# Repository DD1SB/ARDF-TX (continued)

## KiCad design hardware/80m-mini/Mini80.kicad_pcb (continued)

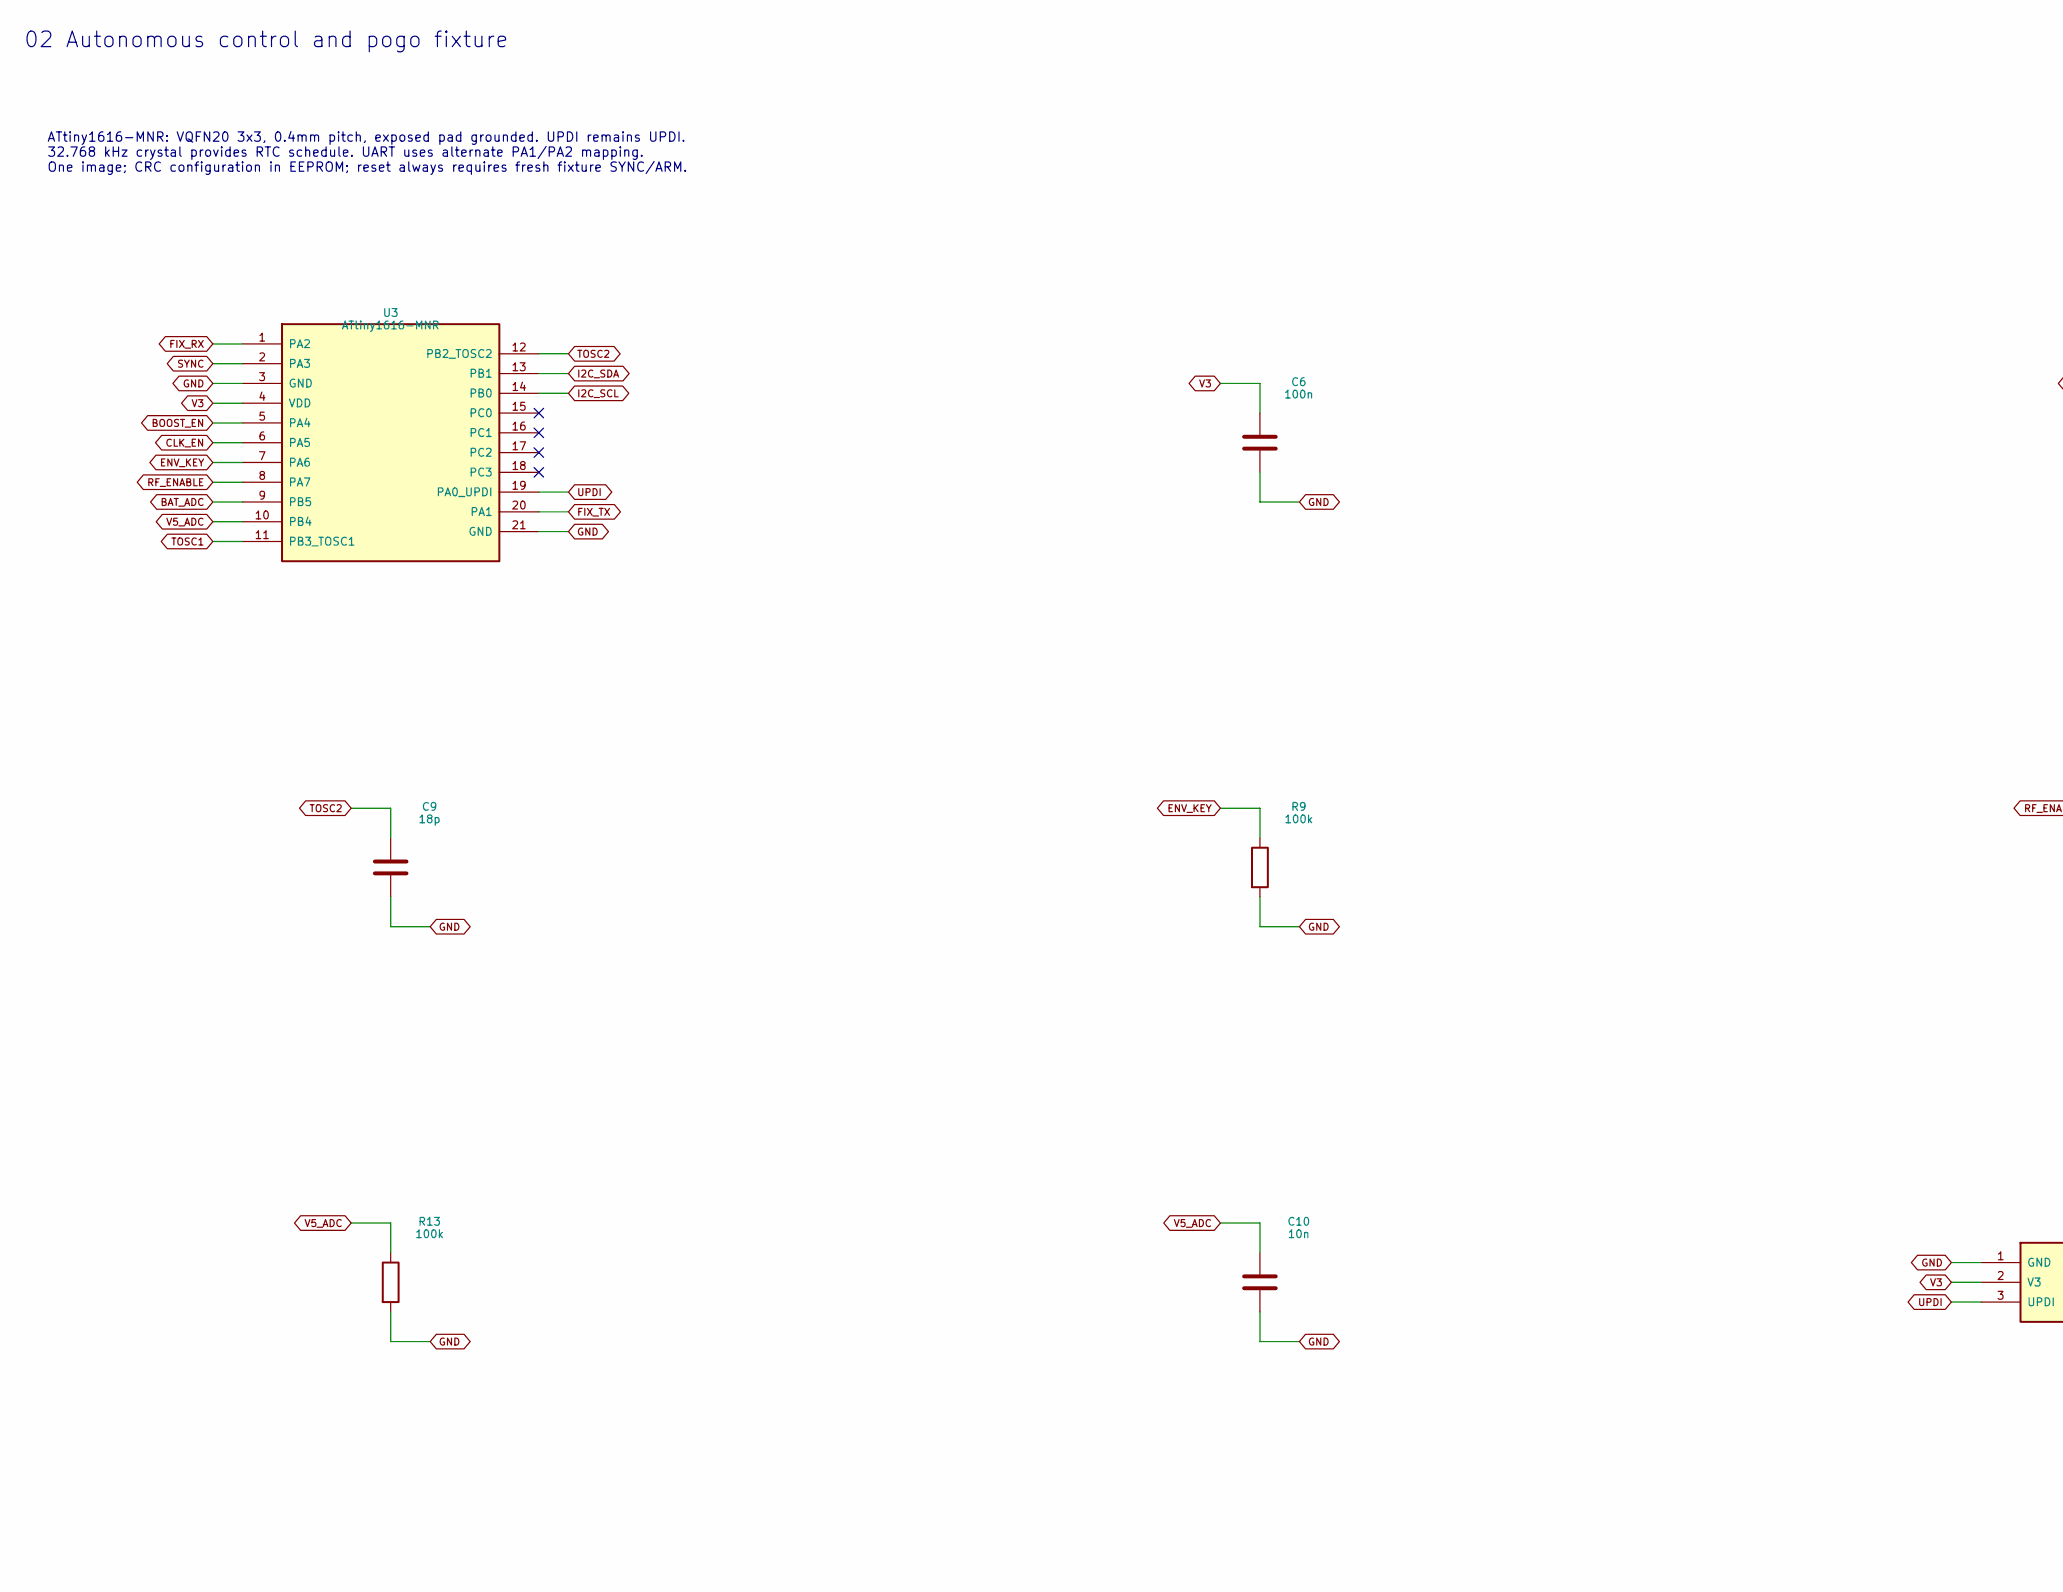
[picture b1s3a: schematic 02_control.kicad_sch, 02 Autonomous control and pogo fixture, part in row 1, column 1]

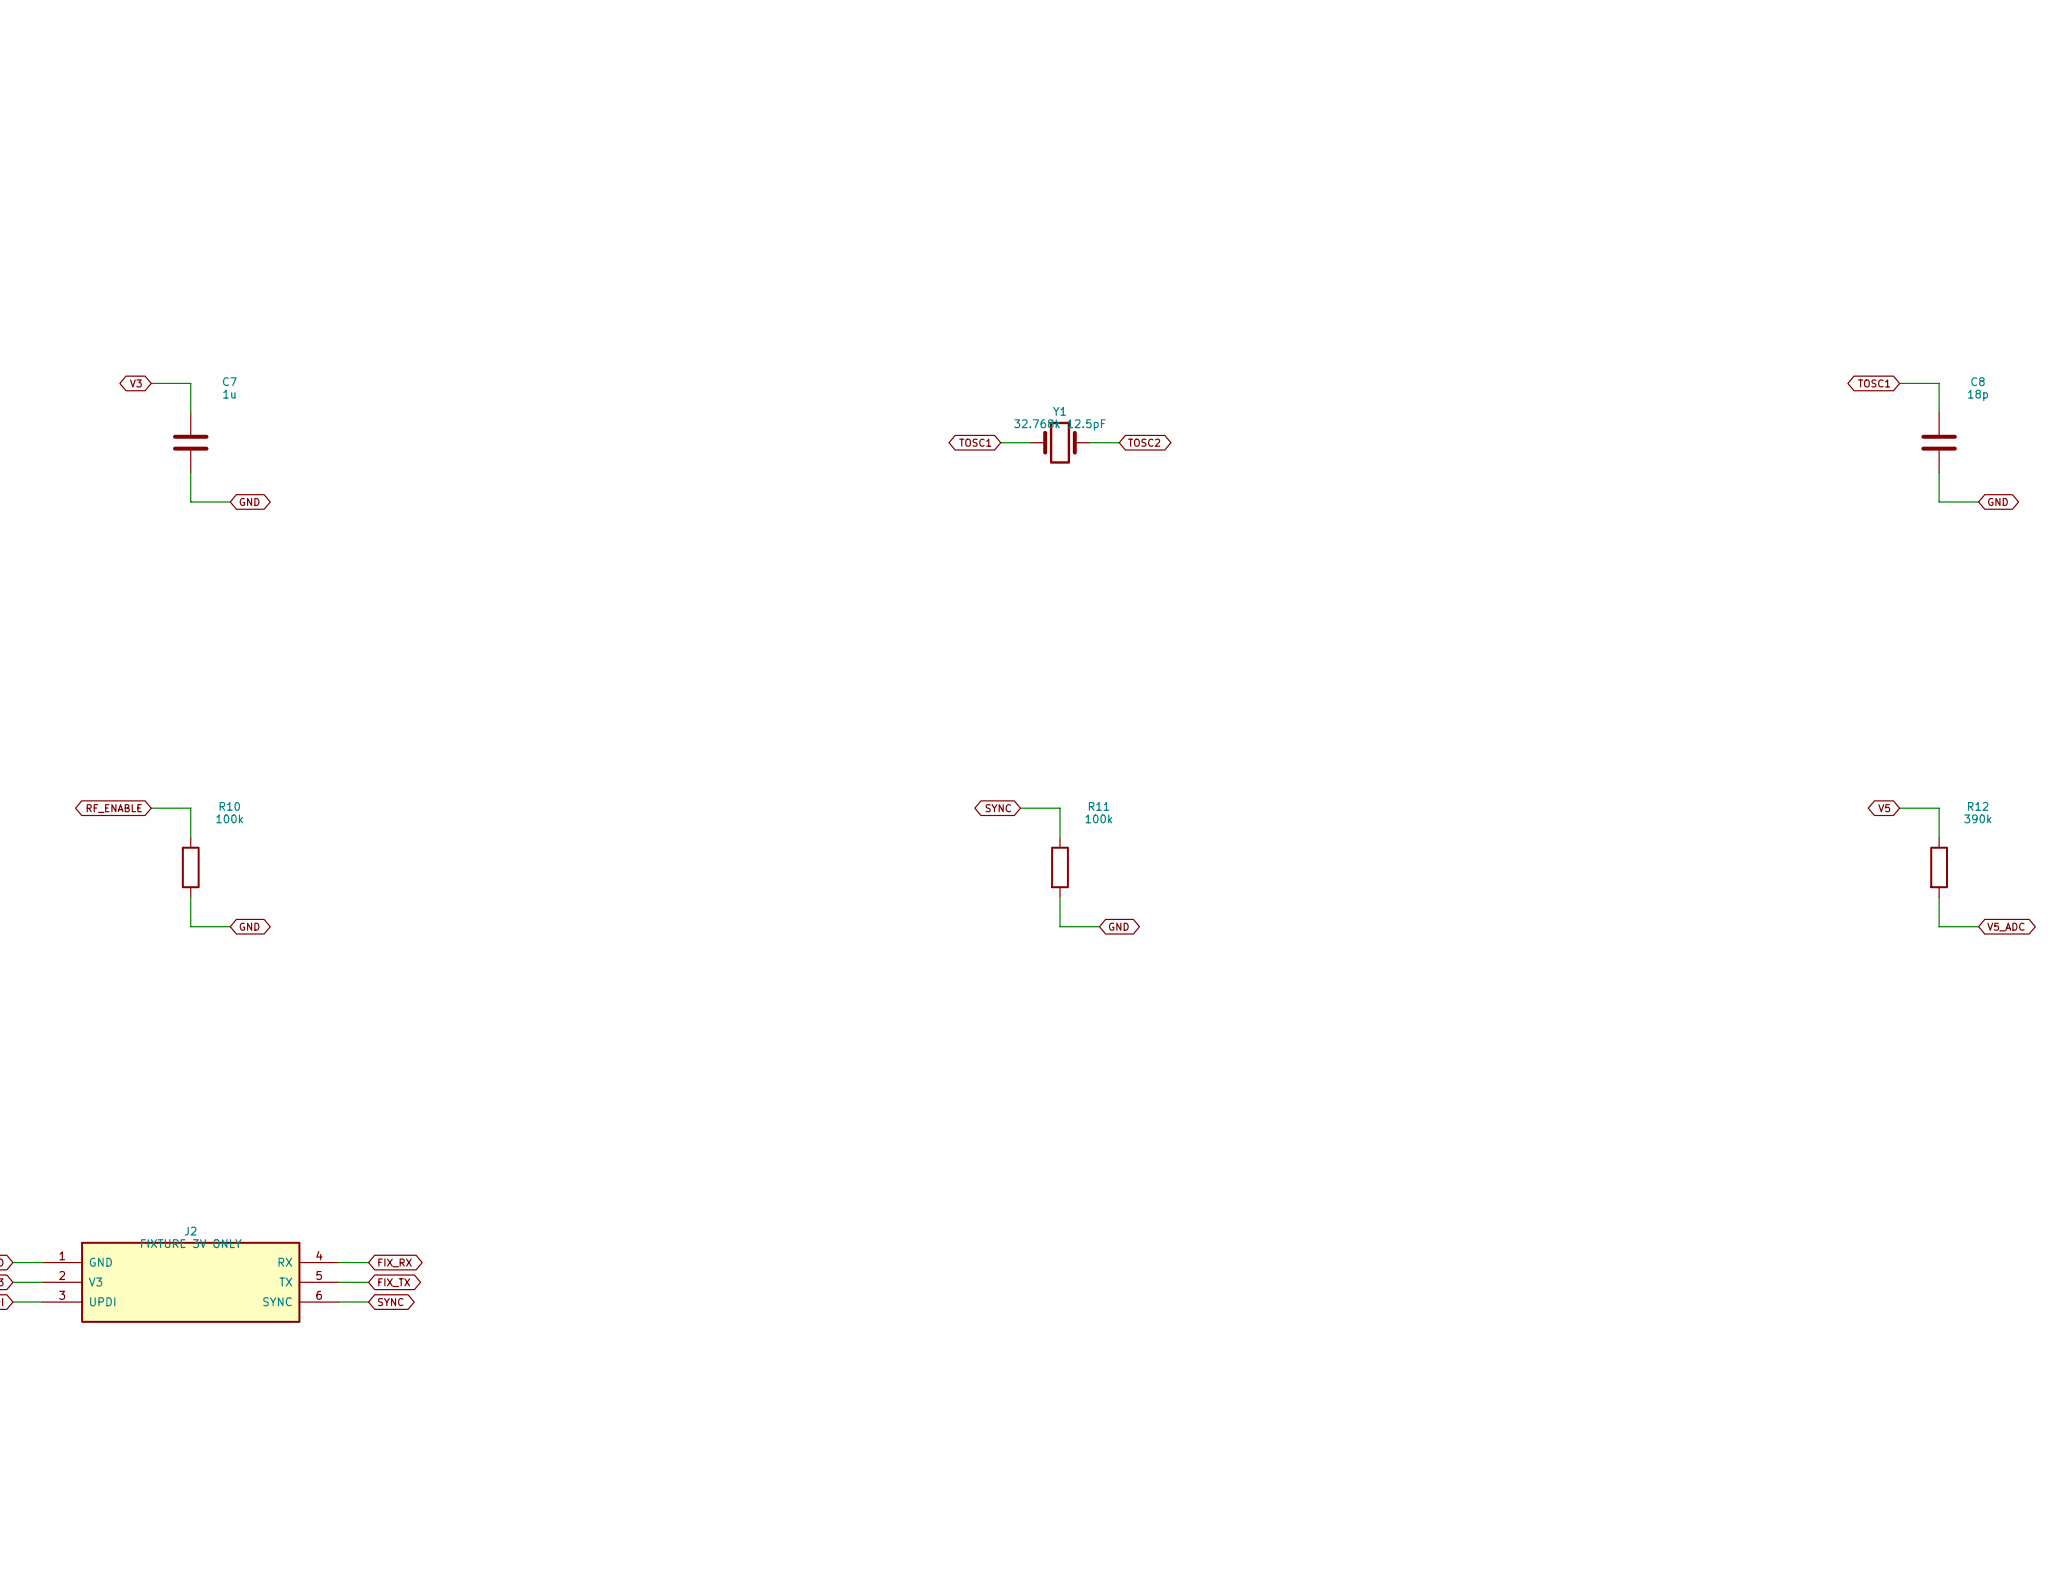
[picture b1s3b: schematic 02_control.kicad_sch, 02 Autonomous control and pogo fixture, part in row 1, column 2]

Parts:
C6: 100n; C_0402_1005Metric; MPN CL05B104KO5NNNC
C7: 1u; C_0402_1005Metric; MPN GRM155R61A105KE15D
C8, C9: 18p; C_0402_1005Metric; MPN GRM1555C1H180JA01D
C10: 10n; C_0402_1005Metric; MPN GRM155R71H103KA88D
J2: FIXTURE 3V ONLY; Pogo6; MPN PCB feature
R9, R10, R11, R13: 100k; R_0402_1005Metric; MPN RC0402FR-07100KL
R12: 390k; R_0402_1005Metric; MPN RC0402FR-07390KL
U3: ATtiny1616-MNR; ATtiny1616_VQFN20_JLC; MPN ATTINY1616-MNR
Y1: 32.768k 12.5pF; Crystal_SMD_3215-2Pin_3.2x1.5mm; MPN ABS07-32.768KHZ-T

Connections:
BAT_ADC: U3.9 (PB5); also elsewhere on the board
BOOST_EN: U3.5 (PA4); also elsewhere on the board
CLK_EN: U3.6 (PA5); also elsewhere on the board
ENV_KEY: R9.1, U3.7 (PA6); also elsewhere on the board
FIX_RX: J2.4 (RX), U3.1 (PA2)
FIX_TX: J2.5 (TX), U3.20 (PA1)
GND: C6.2, C7.2, C8.2, C9.2, C10.2, J2.1 (GND), R9.2, R10.2, R11.2, R13.2, U3.3 (GND), U3.21 (GND); also elsewhere on the board
I2C_SCL: U3.14 (PB0); also elsewhere on the board
I2C_SDA: U3.13 (PB1); also elsewhere on the board
RF_ENABLE: R10.1, U3.8 (PA7); also elsewhere on the board
SYNC: J2.6 (SYNC), R11.1, U3.2 (PA3)
TOSC1: C8.1, U3.11 (PB3_TOSC1), Y1.1
TOSC2: C9.1, U3.12 (PB2_TOSC2), Y1.2
UPDI: J2.3 (UPDI), U3.19 (PA0_UPDI)
V3: C6.1, C7.1, J2.2 (V3), U3.4 (VDD); also elsewhere on the board
V5: R12.1; also elsewhere on the board
V5_ADC: C10.1, R12.2, R13.1, U3.10 (PB4)

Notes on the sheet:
02 Autonomous control and pogo fixture
ATtiny1616-MNR: VQFN20 3x3, 0.4mm pitch, exposed pad grounded. UPDI remains UPDI. 32.768 kHz crystal provides RTC schedule. UART uses alternate PA1/PA2 mapping. One image; CRC configuration in EEPROM; reset always requires fresh fixture SYNC/ARM.
M80-E1: REVIEW / ALL hardware measurements NOT RUN / unbuilt engineering candidate.

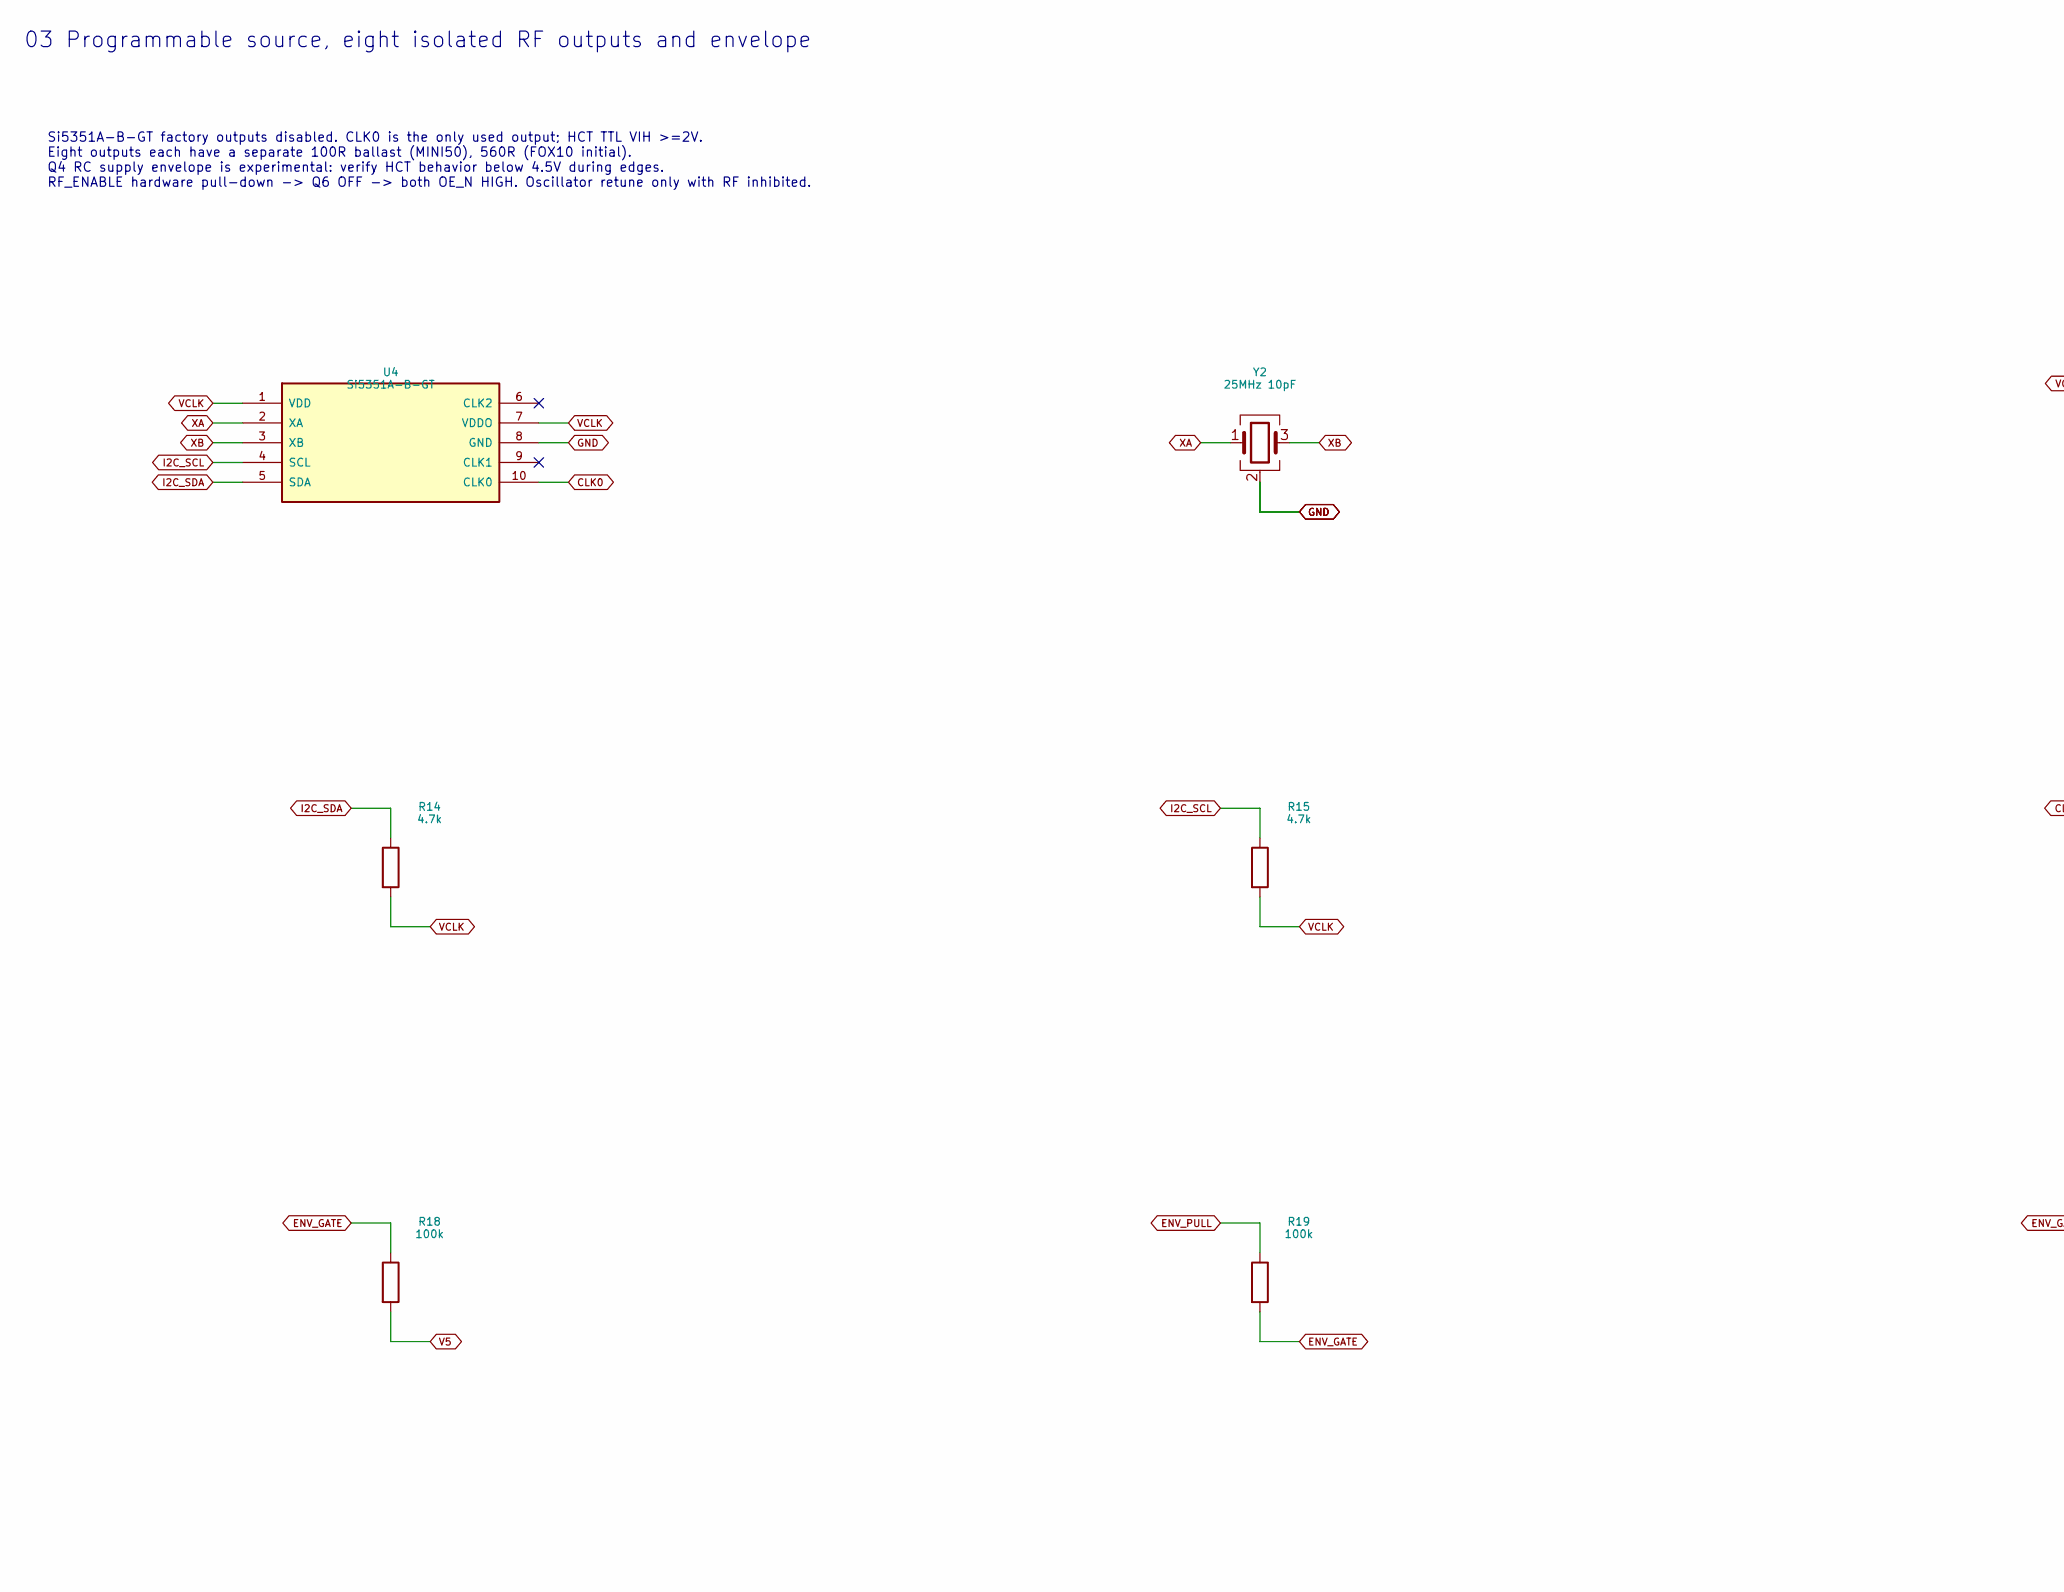
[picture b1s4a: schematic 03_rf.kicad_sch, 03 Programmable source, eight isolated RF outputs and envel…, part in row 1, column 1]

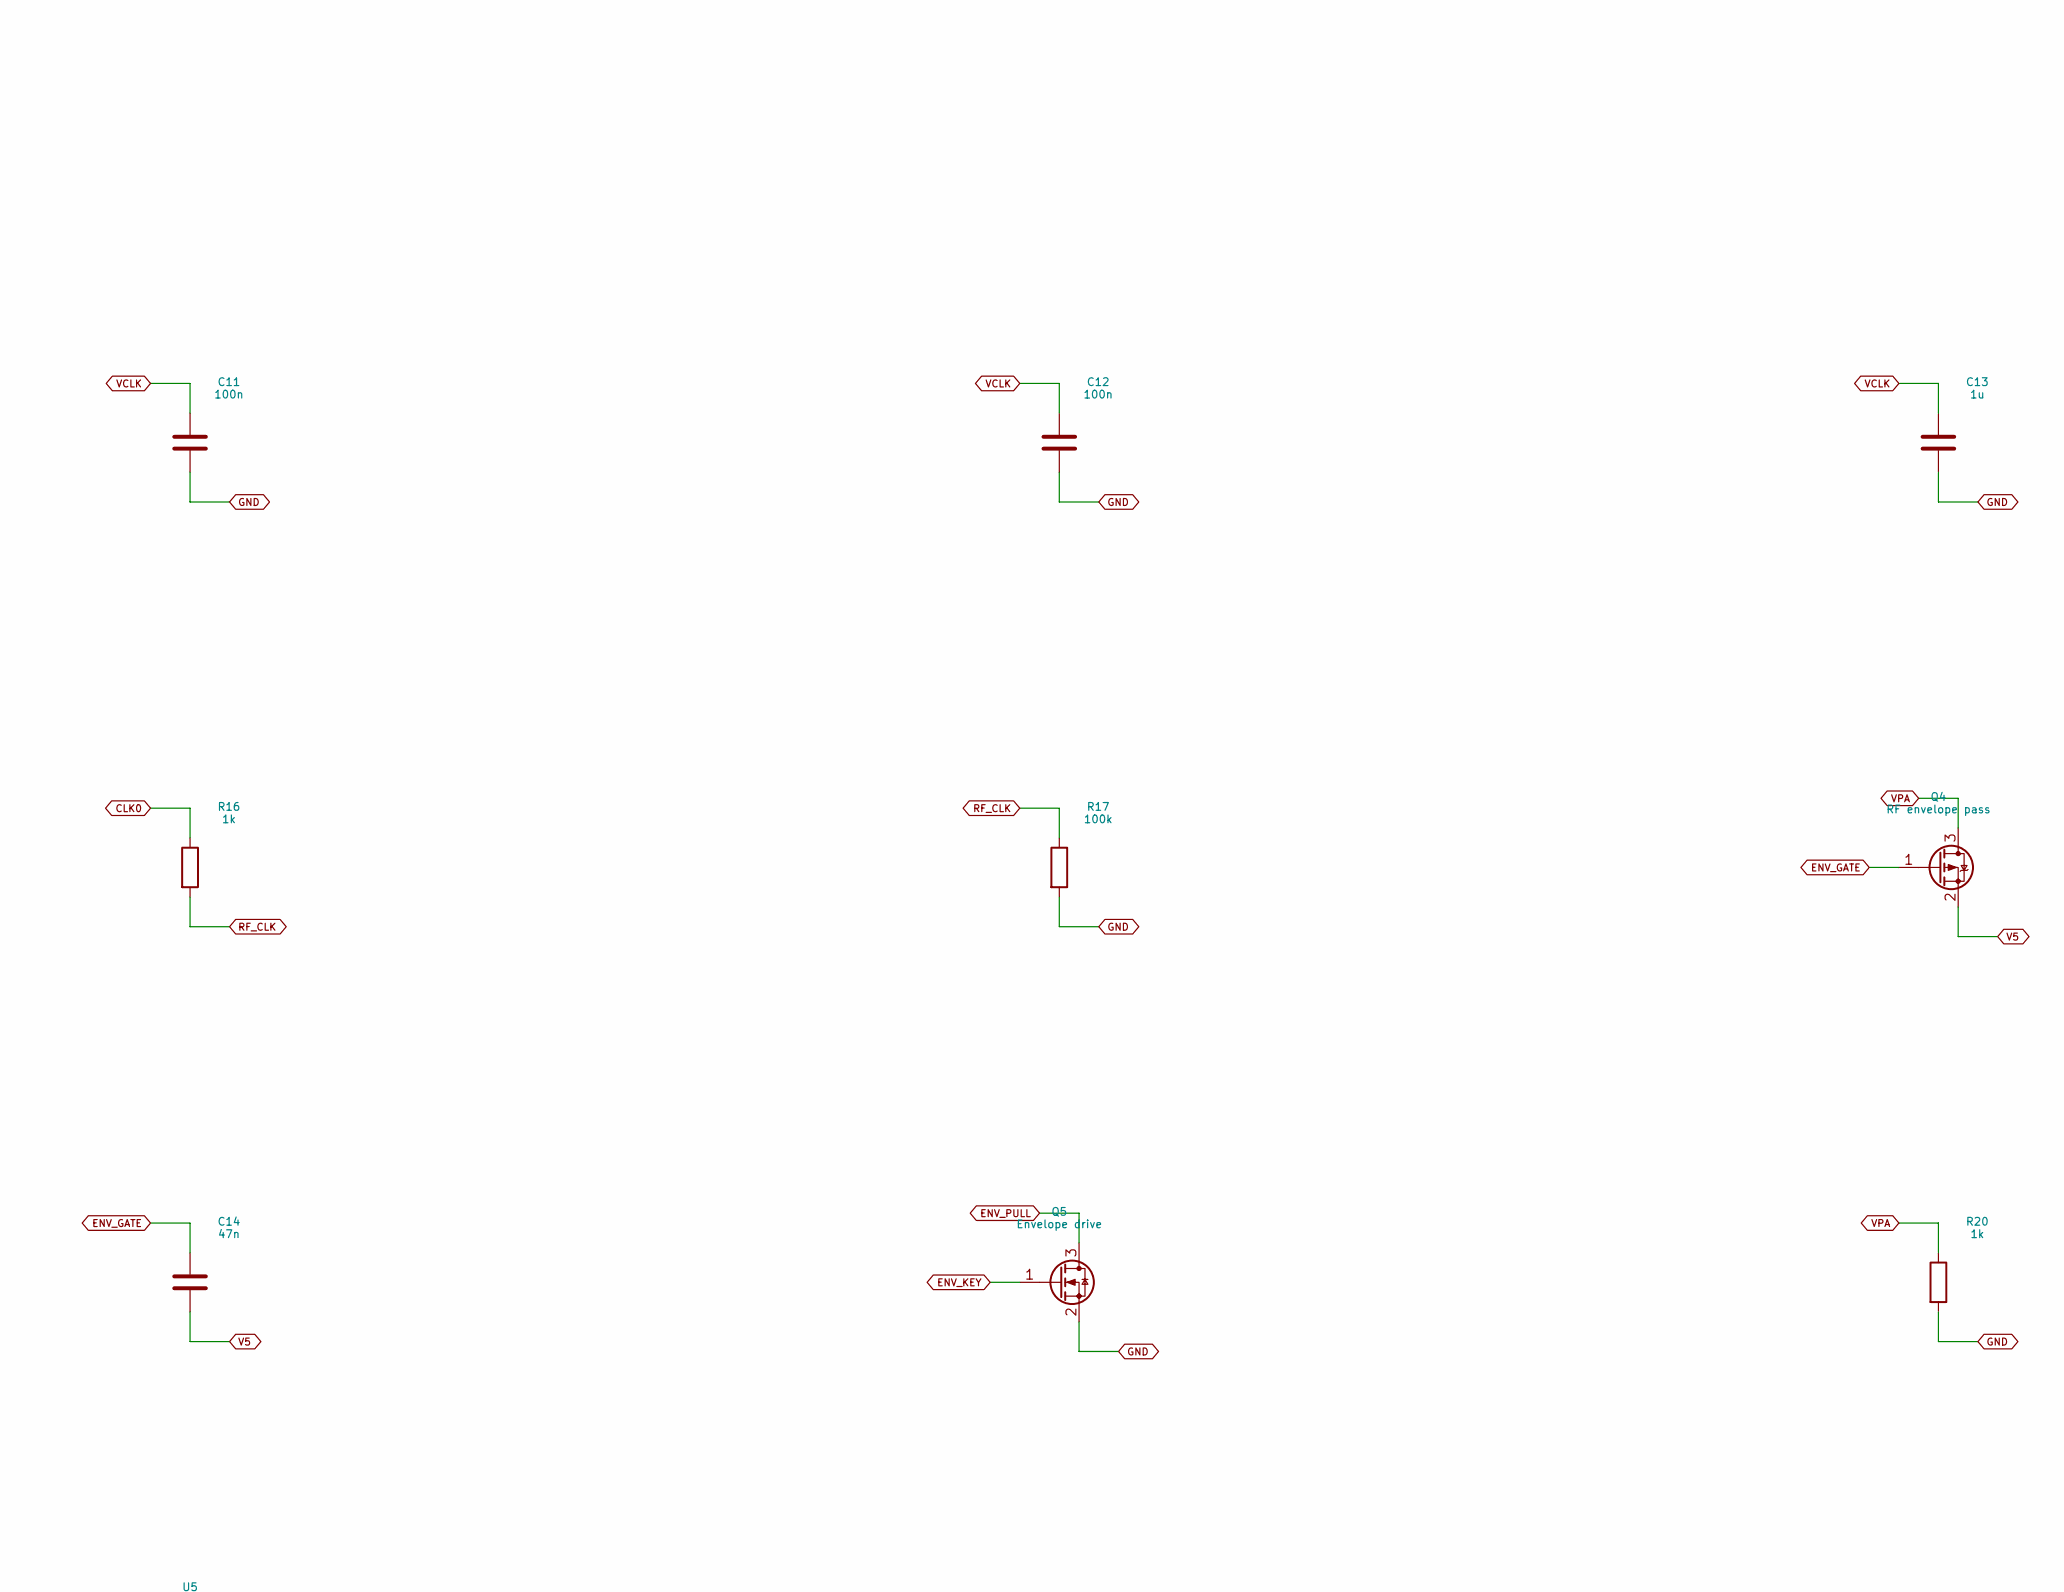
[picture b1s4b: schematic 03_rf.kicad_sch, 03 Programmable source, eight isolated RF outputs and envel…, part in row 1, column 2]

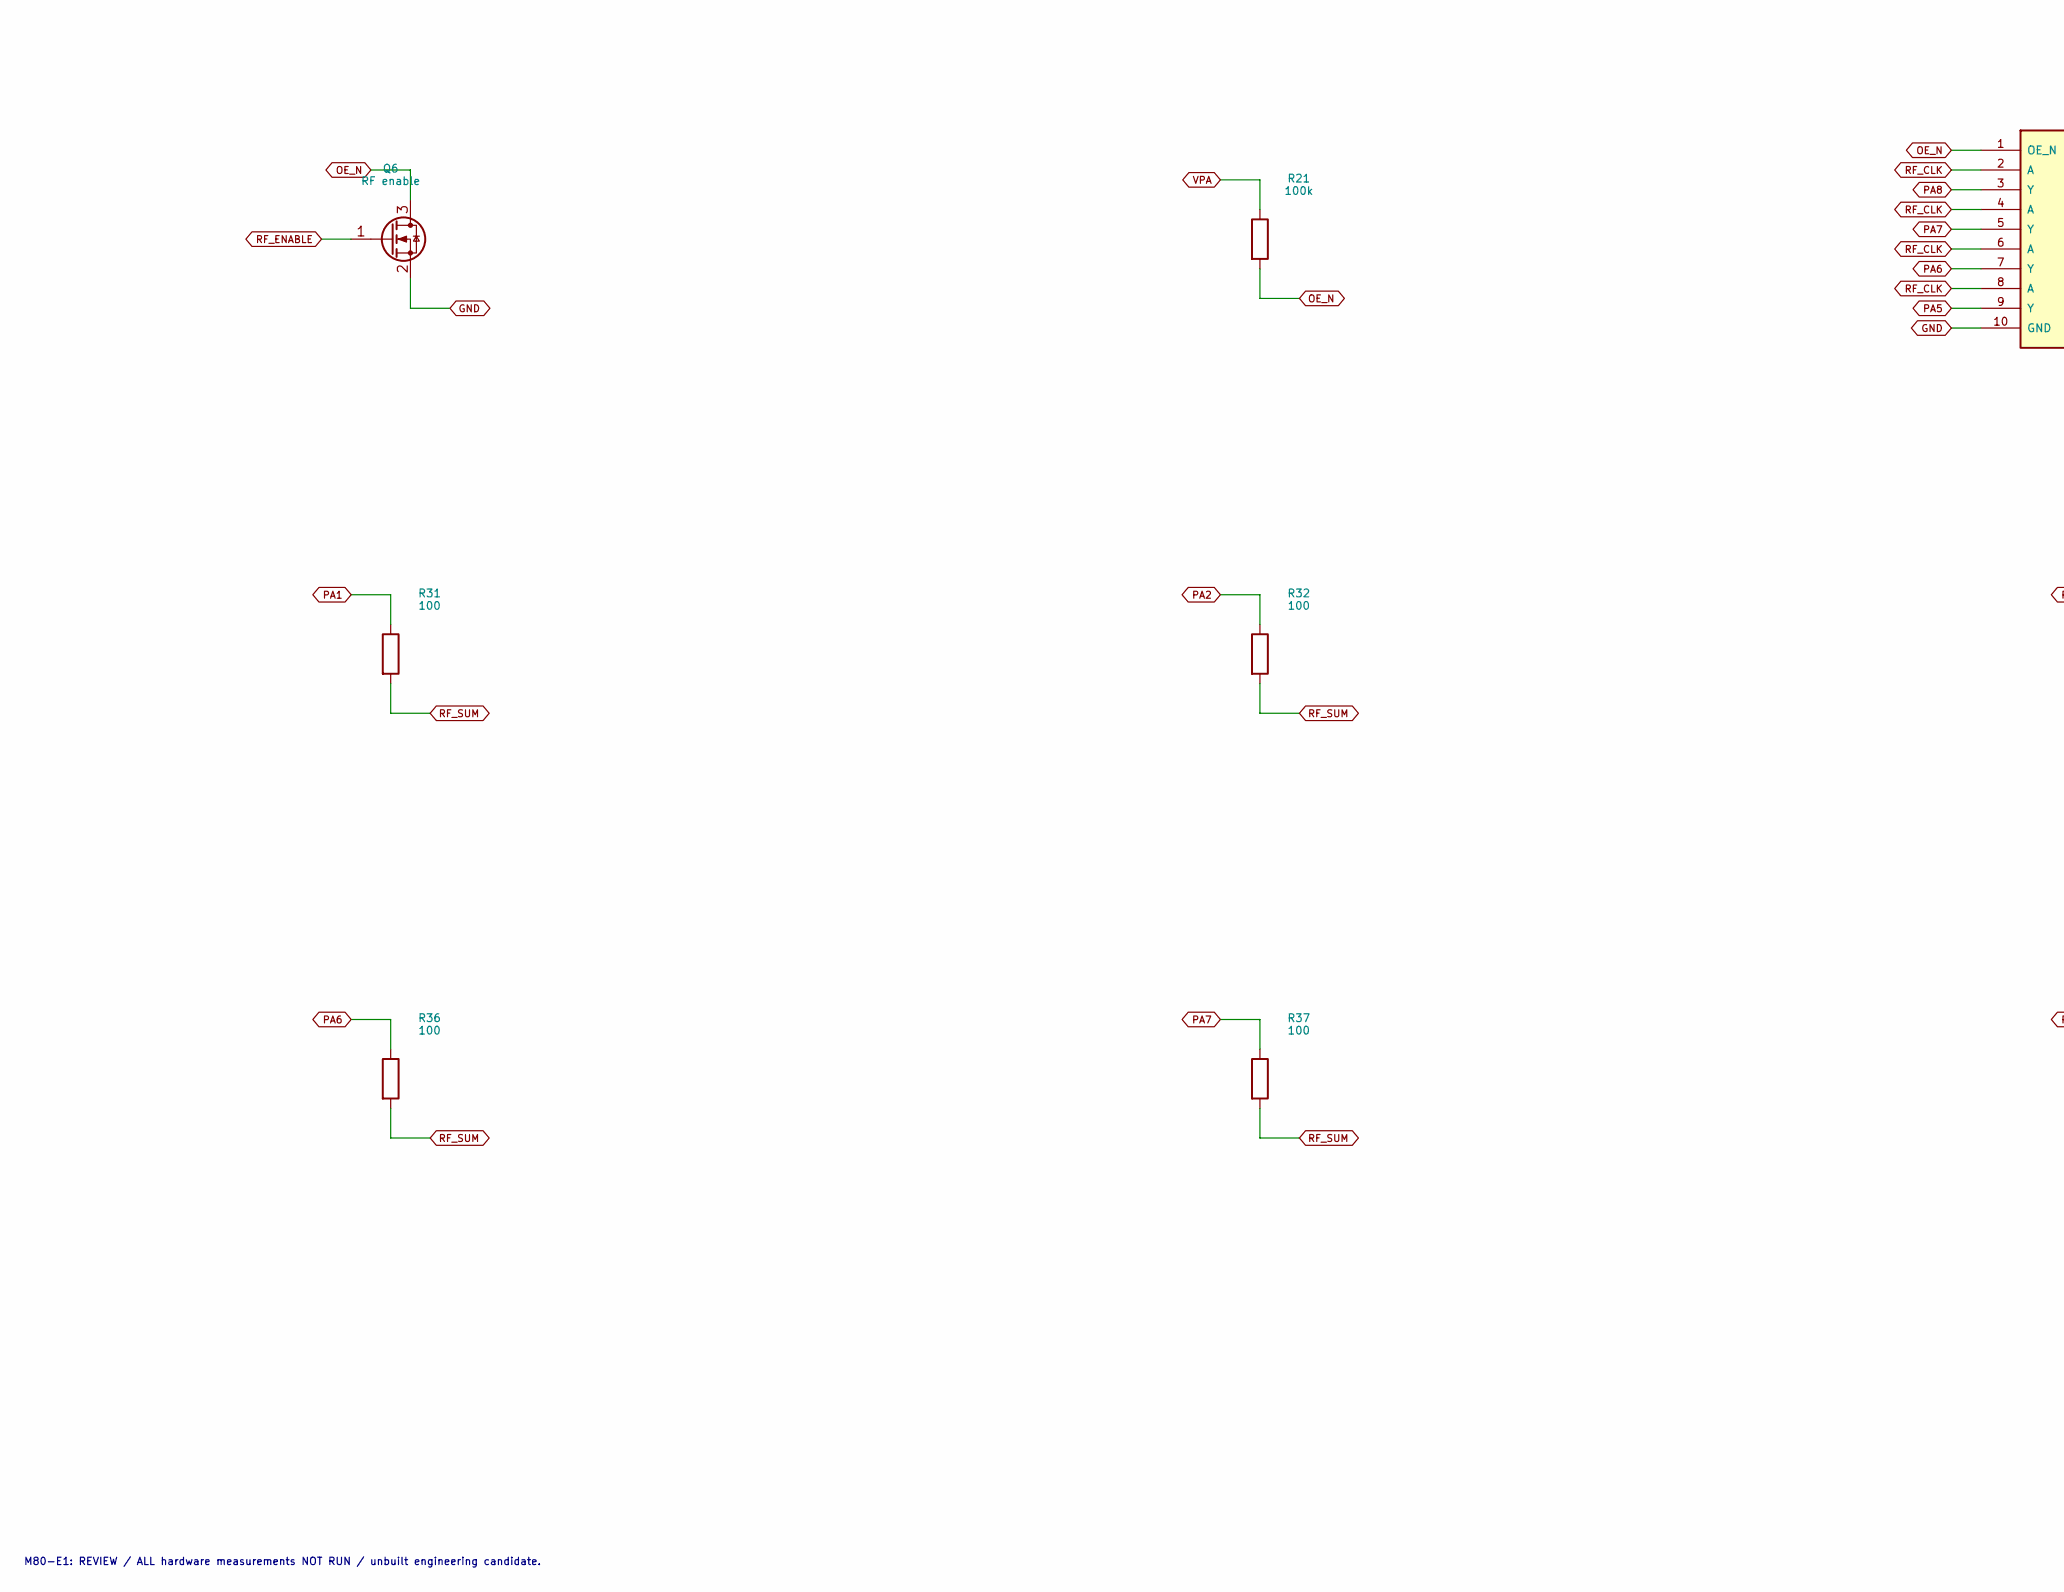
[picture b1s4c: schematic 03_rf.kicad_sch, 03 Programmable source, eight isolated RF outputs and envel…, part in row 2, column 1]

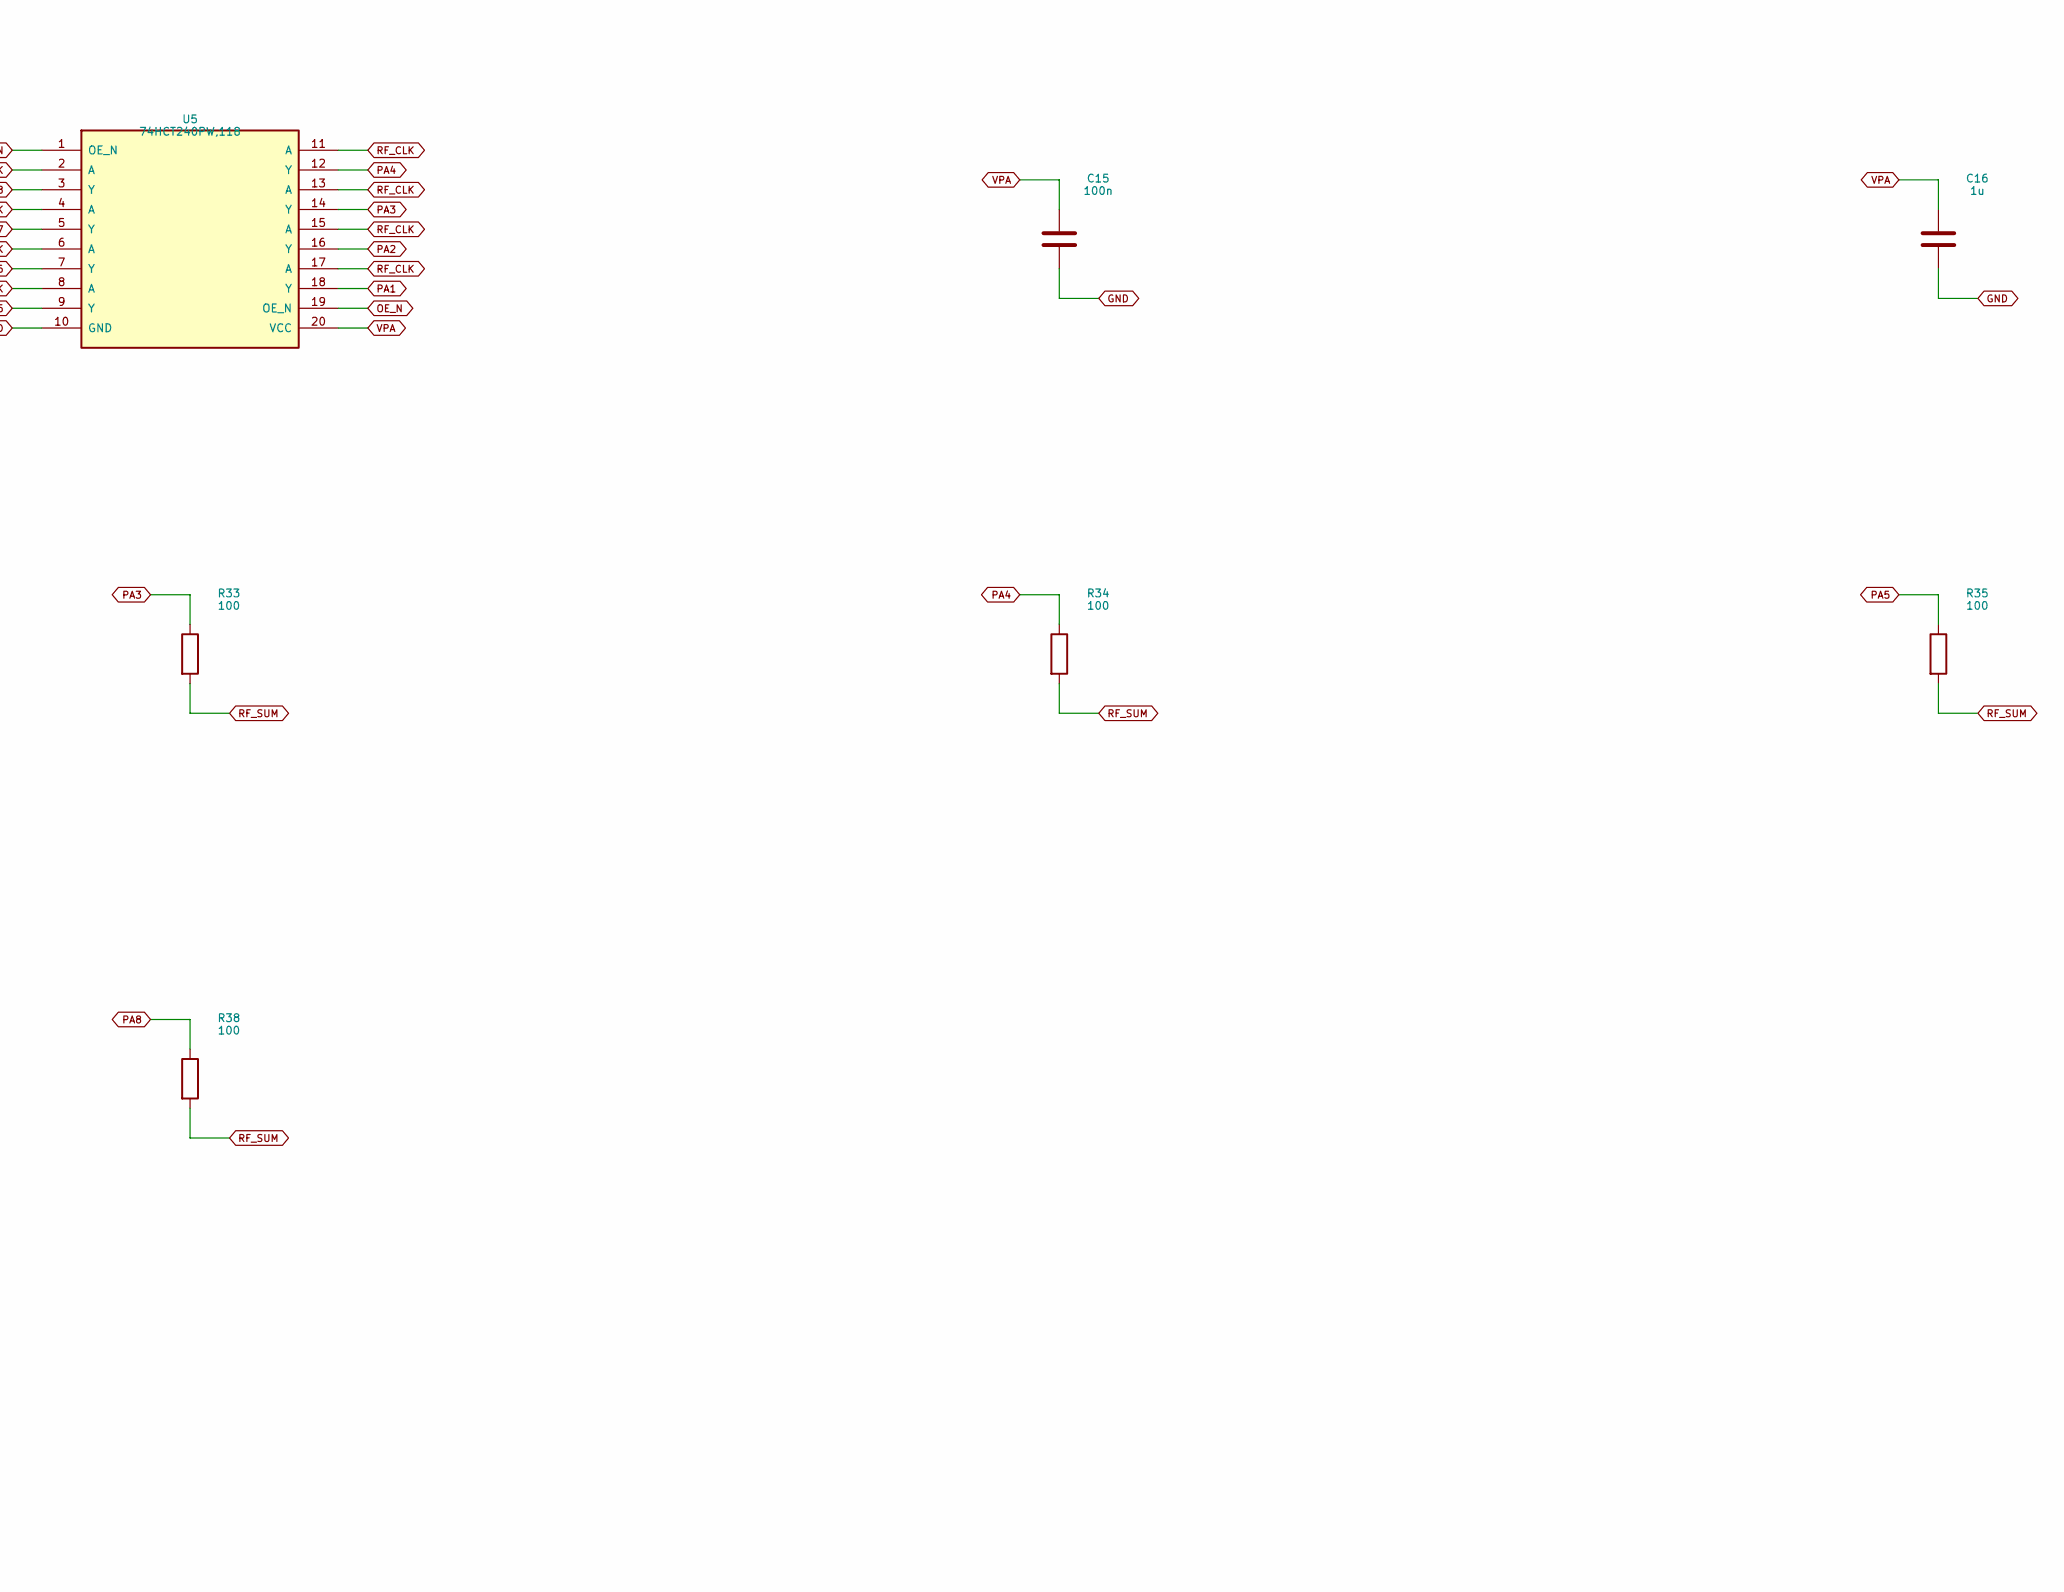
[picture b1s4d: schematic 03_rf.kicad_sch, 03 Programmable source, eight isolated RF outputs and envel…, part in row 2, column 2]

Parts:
C11, C12, C15: 100n; C_0402_1005Metric; MPN CL05B104KO5NNNC
C13, C16: 1u; C_0402_1005Metric; MPN GRM155R61A105KE15D
C14: 47n; C_0402_1005Metric; MPN GRM155R71C473KA01D
Q4: RF envelope pass; SOT-23; MPN DMP2035U-7
Q5: Envelope drive; SOT-23; MPN 2N7002,215
Q6: RF enable; SOT-23; MPN 2N7002,215
R14, R15: 4.7k; R_0402_1005Metric; MPN RC0402FR-074K7L
R16, R20: 1k; R_0402_1005Metric; MPN RC0402FR-071KL
R17, R18, R19, R21: 100k; R_0402_1005Metric; MPN RC0402FR-07100KL
R31, R32, R33, R34, R35, R36, R37, R38: 100; R_0402_1005Metric; MPN RC0402FR-07100RL
U4: Si5351A-B-GT; MSOP-10_3x3mm_P0.5mm; MPN SI5351A-B-GT
U5: 74HCT240PW,118; TSSOP-20_4.4x6.5mm_P0.65mm; MPN 74HCT240PW,118
Y2: 25MHz 10pF; Crystal_SMD_3225-4Pin_3.2x2.5mm; MPN CX3225FB25000F0FZZH1

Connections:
CLK0: R16.1, U4.10 (CLK0); also elsewhere on the board
ENV_GATE: C14.1, Q4.1 (G), R18.1, R19.2
ENV_KEY: Q5.1 (G); also elsewhere on the board
ENV_PULL: Q5.3 (D), R19.1
GND: C11.2, C12.2, C13.2, C15.2, C16.2, Q5.2 (S), Q6.2 (S), R17.2, R20.2, U4.8 (GND), U5.10 (GND), Y2.2 (G), Y2.4 (G); also elsewhere on the board
I2C_SCL: R15.1, U4.4 (SCL); also elsewhere on the board
I2C_SDA: R14.1, U4.5 (SDA); also elsewhere on the board
OE_N: Q6.3 (D), R21.2, U5.1 (OE_N), U5.19 (OE_N); also elsewhere on the board
PA1: R31.1, U5.18 (Y)
PA2: R32.1, U5.16 (Y)
PA3: R33.1, U5.14 (Y)
PA4: R34.1, U5.12 (Y)
PA5: R35.1, U5.9 (Y)
PA6: R36.1, U5.7 (Y)
PA7: R37.1, U5.5 (Y)
PA8: R38.1, U5.3 (Y)
RF_CLK: R16.2, R17.1, U5.2 (A), U5.4 (A), U5.6 (A), U5.8 (A), U5.11 (A), U5.13 (A), U5.15 (A), U5.17 (A)
RF_ENABLE: Q6.1 (G); also elsewhere on the board
RF_SUM: R31.2, R32.2, R33.2, R34.2, R35.2, R36.2, R37.2, R38.2; also elsewhere on the board
V5: C14.2, Q4.2 (S), R18.2; also elsewhere on the board
VCLK: C11.1, C12.1, C13.1, R14.2, R15.2, U4.1 (VDD), U4.7 (VDDO); also elsewhere on the board
VPA: C15.1, C16.1, Q4.3 (D), R20.1, R21.1, U5.20 (VCC); also elsewhere on the board
XA: U4.2 (XA), Y2.1
XB: U4.3 (XB), Y2.3

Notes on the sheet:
03 Programmable source, eight isolated RF outputs and envelope
Si5351A-B-GT factory outputs disabled. CLK0 is the only used output; HCT TTL VIH >=2V. Eight outputs each have a separate 100R ballast (MINI50), 560R (FOX10 initial). Q4 RC supply envelope is experimental: verify HCT behavior below 4.5V during edges. RF_ENABLE hardware pull-down -> Q6 OFF -> both O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
M80-E1: REVIEW / ALL hardware measurements NOT RUN / unbuilt engineering candidate.
